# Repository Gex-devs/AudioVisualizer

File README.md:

# STM32 Audio visualizer DOT MATRIX

Audio Visualizer based on STM32 bluepill utilizing Fast FFT and hacky trick to make the Matrix LED working nicely together. 

## Compact Size

Made a Add-on type PCB that laches on the back of the LED matrix.

## Components 
The Audio Visualizer features Real-time audio visualization with Fast Fourier Transform (FFT) to accurately visualize real audio frequencies rather than just detecting high or low noise levels.

* STM32 Bluepill
* MAX4466 Microphone Module
* 8x8 Matrix LED * 4

## Software Used

* [Kicad](https://www.kicad.org/) : PCB Design 
* [STM32MAX](https://www.st.com/en/development-tools/stm32cubemx.html) : Project Configurator 
* [T-filter](http://t-filter.engineerjs.com/) : Desgning Fir filter

## Tools Used

* Lab power supply
* Oscilloscope 
* ST-LINK/V2 debugger

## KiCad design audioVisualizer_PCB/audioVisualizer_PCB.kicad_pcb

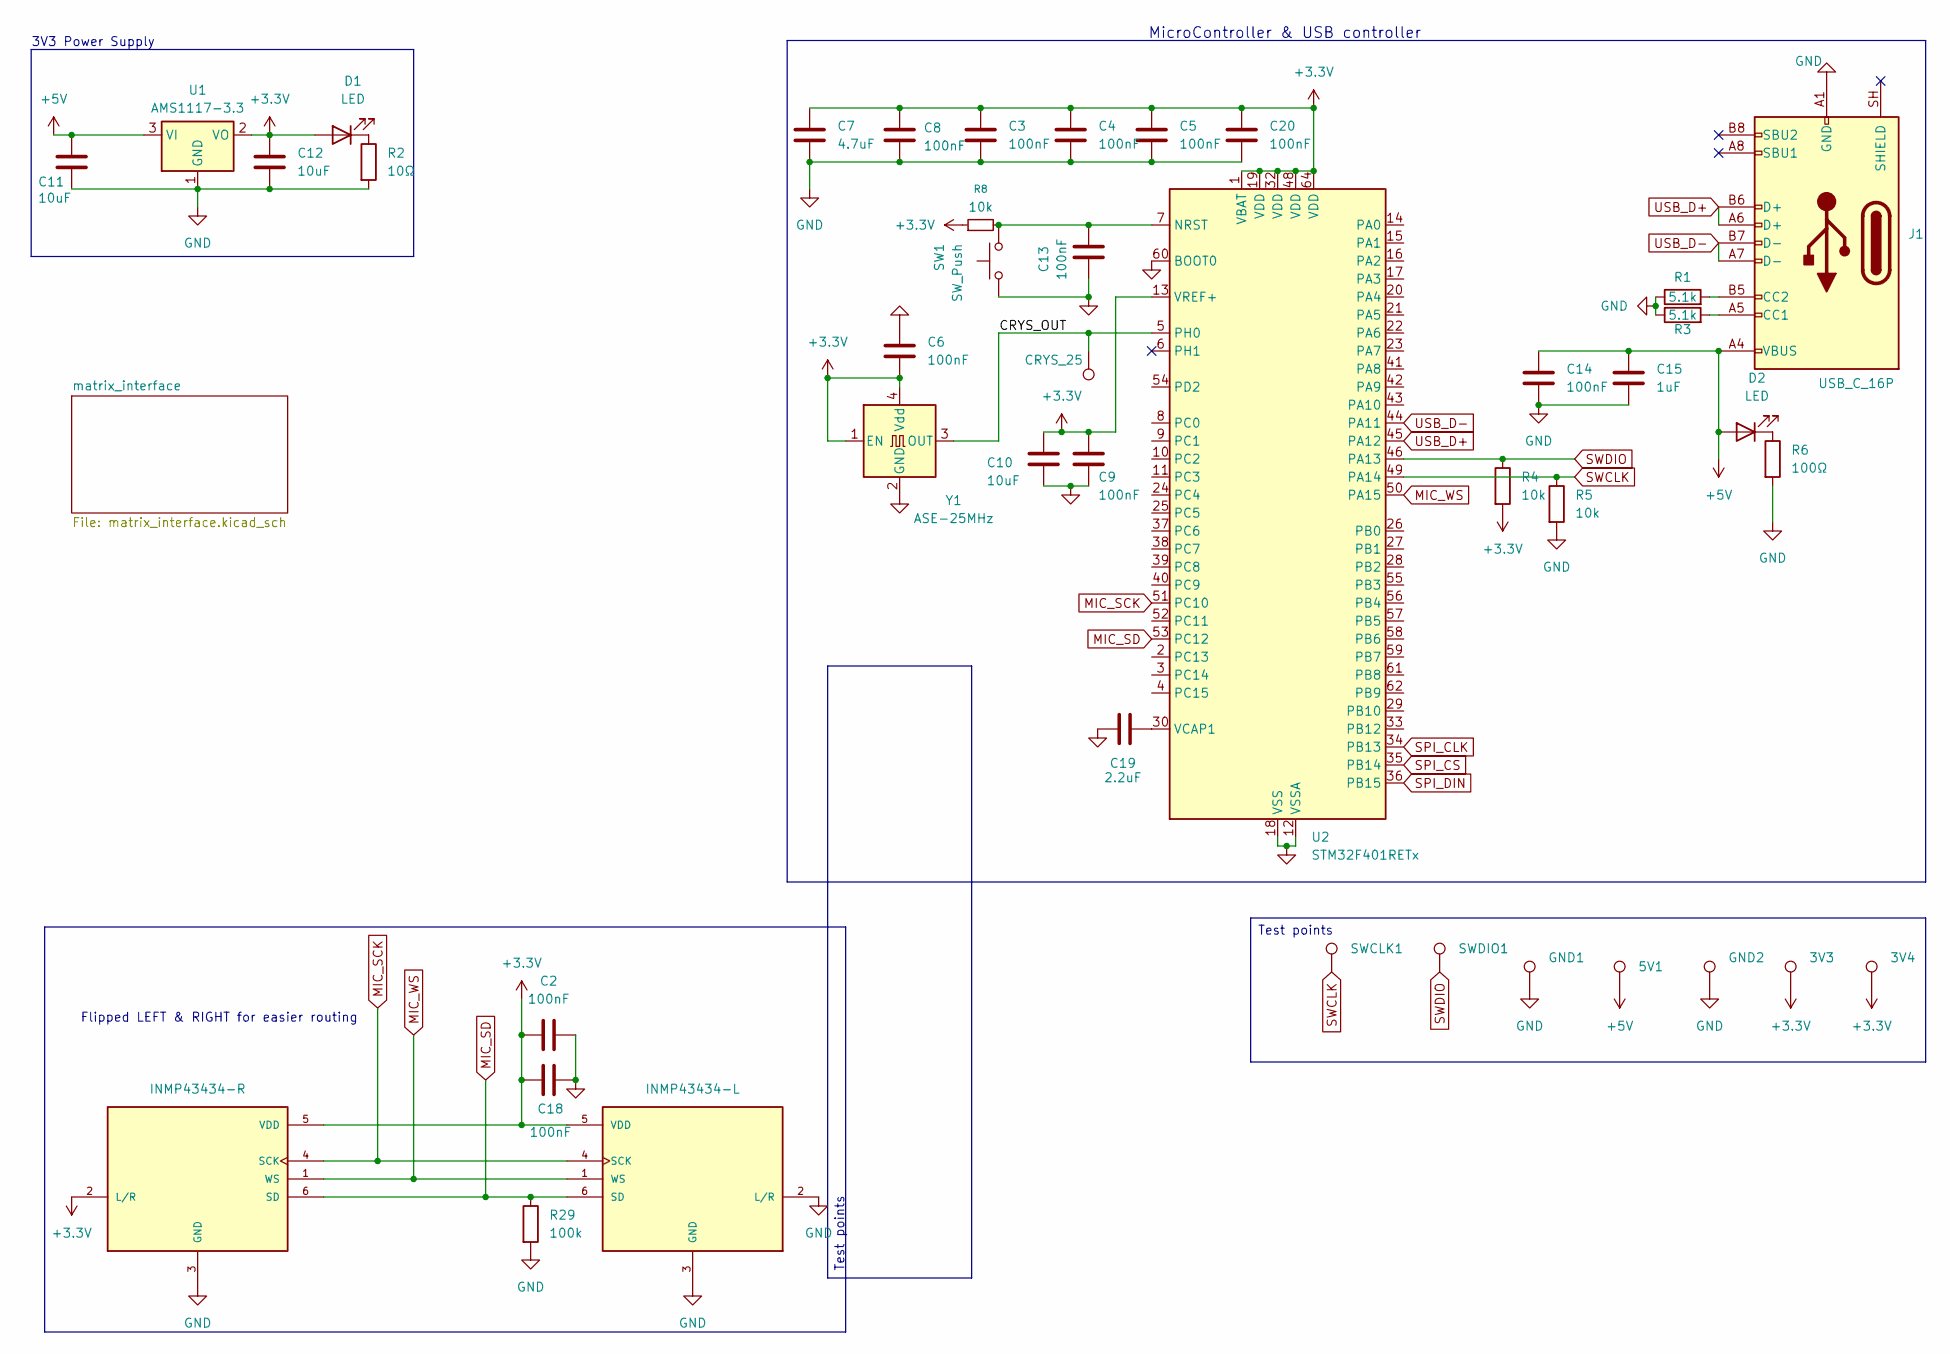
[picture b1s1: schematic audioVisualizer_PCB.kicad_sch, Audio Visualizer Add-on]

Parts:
3V3, 3V4, 5V1: TestPoint_Keystone_5015_Micro_Mini
C2, C3, C6, C8, C9, C13, C18, C20: 100nF; C_0805_2012Metric
C4, C5, C14: 100nF; C_0402_1005Metric
C7: 4.7uF; C_0805_2012Metric
C10, C11, C12: 10uF; C_0805_2012Metric
C15: 1uF; C_0402_1005Metric
C19: 2.2uF; C_0402_1005Metric
CRYS_25: CRYS_25; TestPoint_Keystone_5015_Micro_Mini
D1, D2: LED; LED_0805_2012Metric
GND1, GND2: TestPoint_Keystone_5015_Micro_Mini
J1: USB_C_16P; USB_C_Receptacle_GCT_USB4105-xx-A_16P_TopMnt_Horizontal
MK-L1: INMP43434-R; MIC_ICS-43434; PARTREV 1.1
MK-R1: INMP43434-L; MIC_ICS-43434; PARTREV 1.1
R1, R3: 5.1k; R_1206_3216Metric
R2: 10Ω; R_0402_1005Metric
R4, R5, R8: 10k; R_0805_2012Metric
R6: 100Ω; R_0805_2012Metric
R29: 100k; R_0805_2012Metric
SW1: SW_Push; SW_SPST_TS-1088-xR020
SWCLK1: TestPoint_Keystone_5015_Micro_Mini
SWDIO1: TestPoint_Keystone_5015_Micro_Mini
U1: AMS1117-3.3; SOT-223-3_TabPin2
U2: STM32F401RETx; LQFP-64_10x10mm_P0.5mm
Y1: ASE-25MHz; Oscillator_SMD_EuroQuartz_XO32-4Pin_3.2x2.5mm

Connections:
+3.3V: 3V3.1 (1_1), 3V4.1 (1_1), C2.1, C3.1, C4.1, C5.1, C6.2, C7.1, C8.1, C9.1, C10.1, C12.1, C18.2, C20.1, D1.2 (A), MK-L1.2 (L/R), MK-L1.5 (VDD), MK-R1.5 (VDD), R4.2, R8.1, U1.2 (VO), U2.1 (VBAT), U2.13 (VREF+), U2.19 (VDD), U2.32 (VDD), U2.48 (VDD), U2.64 (VDD), Y1.1 (EN), Y1.4 (Vdd)
+5V: 5V1.1 (1_1), C11.1, C14.2, C15.1, D2.2 (A), J1.A4 (VBUS), J1.A9 (VBUS), J1.B4 (VBUS), J1.B9 (VBUS), U1.3 (VI); also elsewhere on the board
/CRYS_OUT: CRYS_25.1 (1_1), U2.5 (PH0), Y1.3 (OUT)
GND: C2.2, C3.2, C4.2, C5.2, C6.1, C7.2, C8.2, C9.2, C10.2, C11.2, C12.2, C13.2, C14.1, C15.2, C18.1, C19.2, C20.2, GND1.1 (1_1), GND2.1 (1_1), J1.A1 (GND), J1.A12 (GND), J1.B1 (GND), J1.B12 (GND), MK-L1.3 (GND), MK-R1.2 (L/R), MK-R1.3 (GND), R1.1, R2.2, R3.1, R5.2, R6.2, R29.2, SW1.1, U1.1 (GND), U2.12 (VSSA), U2.18 (VSS), U2.31 (VSS), U2.47 (VSS), U2.60 (BOOT0), U2.63 (VSS), Y1.2 (GND); also elsewhere on the board
MIC_SCK: MK-L1.4 (SCK), MK-R1.4 (SCK), U2.51 (PC10)
MIC_SD: MK-L1.6 (SD), MK-R1.6 (SD), R29.1, U2.53 (PC12)
MIC_WS: MK-L1.1 (WS), MK-R1.1 (WS), U2.50 (PA15)
unnamed: D1.1 (K), R2.1
unnamed: D2.1 (K), R6.1
unnamed: J1.A5 (CC1), R3.2
unnamed: J1.B5 (CC2), R1.2
unnamed: C13.1, R8.2, SW1.2, U2.7 (NRST)
unnamed: C19.1, U2.30 (VCAP1)
SPI_CLK: U2.34 (PB13); also elsewhere on the board
SPI_CS: U2.35 (PB14); also elsewhere on the board
SPI_DIN: U2.36 (PB15); also elsewhere on the board
SWCLK: R5.1, SWCLK1.1 (1_1), U2.49 (PA14)
SWDIO: R4.1, SWDIO1.1 (1_1), U2.46 (PA13)
USB_D+: J1.A6 (D+), J1.B6 (D+), U2.45 (PA12)
USB_D-: J1.A7 (D-), J1.B7 (D-), U2.44 (PA11)

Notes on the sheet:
MicroController & USB controller
3V3 Power Supply
Flipped LEFT & RIGHT for easier routing
Test points

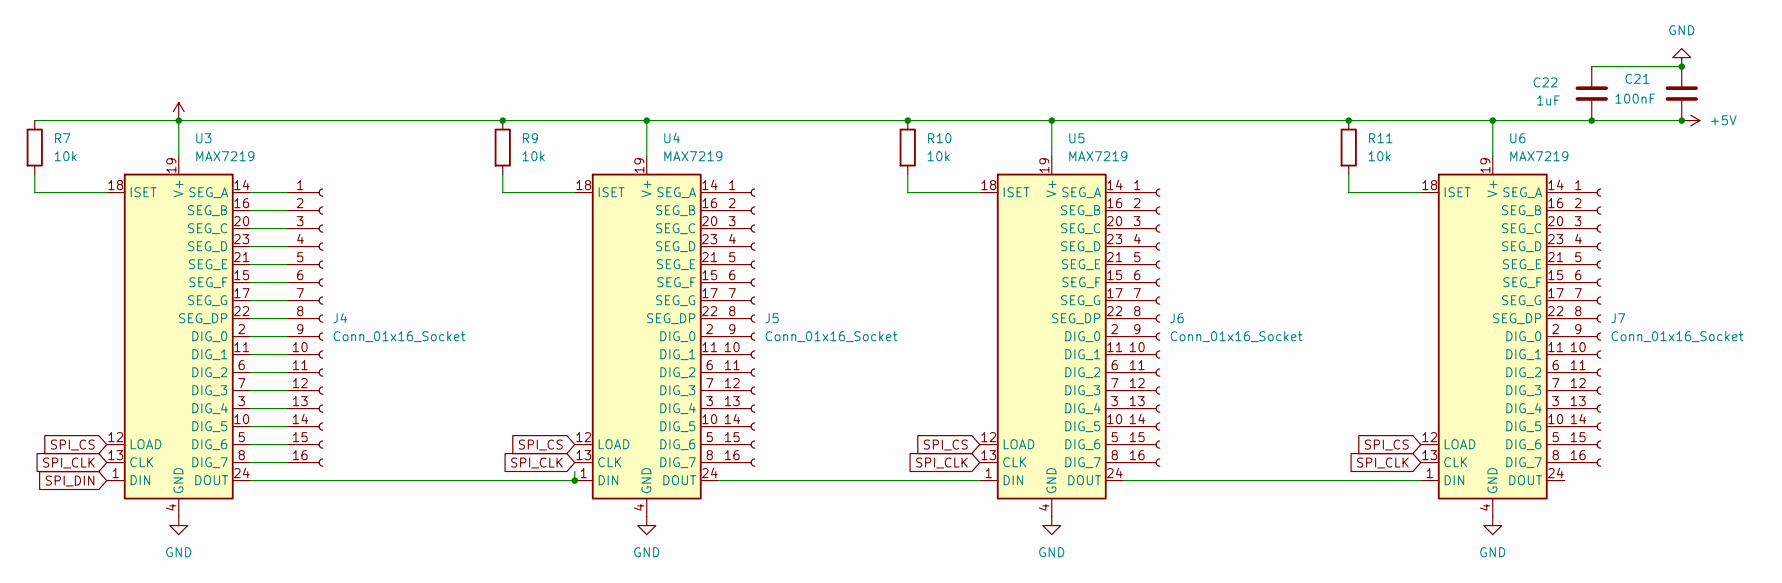
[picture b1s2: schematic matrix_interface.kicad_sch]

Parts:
C21: 100nF; C_0805_2012Metric
C22: 1uF; C_0805_2012Metric
J4, J5, J6, J7: Conn_01x16_Socket; DISPLAY_TA08-81GWA
R7, R9, R10, R11: 10k
U3, U4, U5, U6: MAX7219; SOIC-24W_7.5x15.4mm_P1.27mm

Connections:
+5V: C21.2, C22.1, R7.1, R9.1, R10.1, R11.1, U3.19 (V+), U4.19 (V+), U5.19 (V+), U6.19 (V+); also elsewhere on the board
GND: C21.1, C22.2, U3.4 (GND), U3.9 (GND), U4.4 (GND), U4.9 (GND), U5.4 (GND), U5.9 (GND), U6.4 (GND), U6.9 (GND); also elsewhere on the board
unnamed: J4.1, U3.14 (SEG_A)
unnamed: J4.2, U3.16 (SEG_B)
unnamed: J4.3, U3.20 (SEG_C)
unnamed: J4.4, U3.23 (SEG_D)
unnamed: J4.5, U3.21 (SEG_E)
unnamed: J4.6, U3.15 (SEG_F)
unnamed: J4.7, U3.17 (SEG_G)
unnamed: J4.8, U3.22 (SEG_DP)
unnamed: J4.9, U3.2 (DIG_0)
unnamed: J4.10, U3.11 (DIG_1)
unnamed: J4.11, U3.6 (DIG_2)
unnamed: J4.12, U3.7 (DIG_3)
unnamed: J4.13, U3.3 (DIG_4)
unnamed: J4.14, U3.10 (DIG_5)
unnamed: J4.15, U3.5 (DIG_6)
unnamed: J4.16, U3.8 (DIG_7)
unnamed: J5.1, U4.14 (SEG_A)
unnamed: J5.2, U4.16 (SEG_B)
unnamed: J5.3, U4.20 (SEG_C)
unnamed: J5.4, U4.23 (SEG_D)
unnamed: J5.5, U4.21 (SEG_E)
unnamed: J5.6, U4.15 (SEG_F)
unnamed: J5.7, U4.17 (SEG_G)
unnamed: J5.8, U4.22 (SEG_DP)
unnamed: J5.9, U4.2 (DIG_0)
unnamed: J5.10, U4.11 (DIG_1)
unnamed: J5.11, U4.6 (DIG_2)
unnamed: J5.12, U4.7 (DIG_3)
unnamed: J5.13, U4.3 (DIG_4)
unnamed: J5.14, U4.10 (DIG_5)
unnamed: J5.15, U4.5 (DIG_6)
unnamed: J5.16, U4.8 (DIG_7)
unnamed: J6.1, U5.14 (SEG_A)
unnamed: J6.2, U5.16 (SEG_B)
unnamed: J6.3, U5.20 (SEG_C)
unnamed: J6.4, U5.23 (SEG_D)
unnamed: J6.5, U5.21 (SEG_E)
unnamed: J6.6, U5.15 (SEG_F)
unnamed: J6.7, U5.17 (SEG_G)
unnamed: J6.8, U5.22 (SEG_DP)
unnamed: J6.9, U5.2 (DIG_0)
unnamed: J6.10, U5.11 (DIG_1)
unnamed: J6.11, U5.6 (DIG_2)
unnamed: J6.12, U5.7 (DIG_3)
unnamed: J6.13, U5.3 (DIG_4)
unnamed: J6.14, U5.10 (DIG_5)
unnamed: J6.15, U5.5 (DIG_6)
unnamed: J6.16, U5.8 (DIG_7)
unnamed: J7.1, U6.14 (SEG_A)
unnamed: J7.2, U6.16 (SEG_B)
unnamed: J7.3, U6.20 (SEG_C)
unnamed: J7.4, U6.23 (SEG_D)
unnamed: J7.5, U6.21 (SEG_E)
unnamed: J7.6, U6.15 (SEG_F)
unnamed: J7.7, U6.17 (SEG_G)
unnamed: J7.8, U6.22 (SEG_DP)
unnamed: J7.9, U6.2 (DIG_0)
unnamed: J7.10, U6.11 (DIG_1)
unnamed: J7.11, U6.6 (DIG_2)
unnamed: J7.12, U6.7 (DIG_3)
unnamed: J7.13, U6.3 (DIG_4)
unnamed: J7.14, U6.10 (DIG_5)
unnamed: J7.15, U6.5 (DIG_6)
unnamed: J7.16, U6.8 (DIG_7)
unnamed: U3.24 (DOUT), U4.1 (DIN)
unnamed: R7.2, U3.18 (ISET)
unnamed: U4.24 (DOUT), U5.1 (DIN)
unnamed: R9.2, U4.18 (ISET)
unnamed: U5.24 (DOUT), U6.1 (DIN)
unnamed: R10.2, U5.18 (ISET)
unnamed: R11.2, U6.18 (ISET)
SPI_CLK: U3.13 (CLK), U4.13 (CLK), U5.13 (CLK), U6.13 (CLK); also elsewhere on the board
SPI_CS: U3.12 (LOAD), U4.12 (LOAD), U5.12 (LOAD), U6.12 (LOAD); also elsewhere on the board
SPI_DIN: U3.1 (DIN); also elsewhere on the board

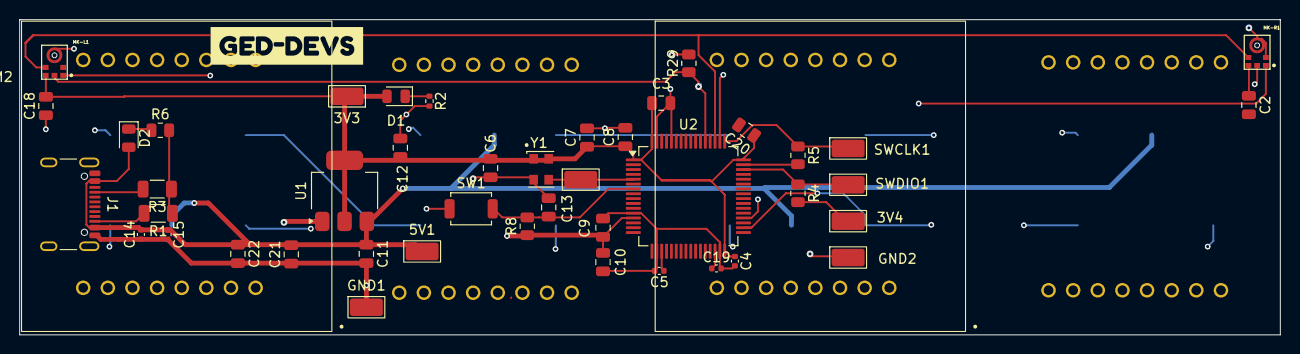
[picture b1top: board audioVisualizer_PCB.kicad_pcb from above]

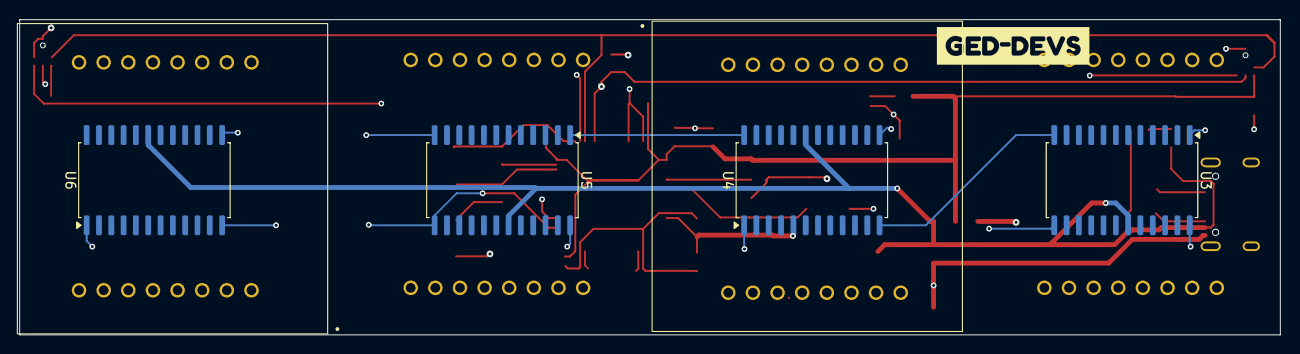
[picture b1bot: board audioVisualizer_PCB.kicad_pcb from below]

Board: 4 copper layers, 130.0 x 32.5 mm, 54 parts (7 on the bottom side), 87 nets.

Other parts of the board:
kibuzzard-69F6314F, kibuzzard-69F6314F#2: G***; kibuzzard-69F6314F

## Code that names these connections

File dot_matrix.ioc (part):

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Mcu.Name=STM32F401R(D-E)Tx
Mcu.Package=LQFP64
Mcu.UserName=STM32F401RETx
PA0-WKUP.Signal=S_TIM2_CH1_ETR
PA11.Mode=Host_Only
PA11.Signal=USB_OTG_FS_DM
PA12.Mode=Host_Only
PA12.Signal=USB_OTG_FS_DP
PA13.Mode=Serial_Wire
PA13.Signal=SYS_JTMS-SWDIO
PA14.Mode=Serial_Wire
PA14.Signal=SYS_JTCK-SWCLK
PA15.Mode=Half_Duplex_Master
PA15.Signal=I2S3_WS
PA9.Mode=Activate_VBUS
PA9.Signal=USB_OTG_FS_VBUS
PB13.Mode=Simplex_Bidirectional_Master
PB13.Signal=SPI2_SCK
PB14.Signal=GPIO_Output
PB15.Mode=Simplex_Bidirectional_Master
PB15.Signal=SPI2_MOSI
PC10.Mode=Half_Duplex_Master
PC10.Signal=I2S3_CK
PC12.Mode=Half_Duplex_Master
PC12.Signal=I2S3_SD
PH0\ -\ OSC_IN.Mode=HSE-External-Clock-Source
PH0\ -\ OSC_IN.Signal=RCC_OSC_IN
PH1\ -\ OSC_OUT.Mode=HSE-External-Clock-Source
PH1\ -\ OSC_OUT.Signal=RCC_OSC_OUT
RCC.HSE_VALUE=25000000
RCC.SYSCLKFreq_VALUE=84000000
RCC.SYSCLKSource=RCC_SYSCLKSOURCE_PLLCLK
board=custom

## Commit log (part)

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2025-04-11 init
2025-04-20 Working module with LED matrix library modification
2025-04-20 Added video and image
2025-07-30 added the working libraries
2025-08-01 applied hann window and added high-pass filter, good visuals
2025-08-01 updated gitignore
2025-08-01 fixed visual mapping, Issue still in Bar index 0 - 10
2025-08-08 added filter, updated ReadME, added PCB
2025-08-08 updated read me
2025-08-08 Moved the interactive BOM to root for deployment
2025-08-19 added fritzing project for prototype
2025-08-19 added image of the Printed pcb
2025-08-28 unfinished workflow and update on the TH of the PCB footprint
2025-08-28 Fixed headerpin diameter, updated workflow
2025-08-28 workflow fix
2025-08-28 Update schematic preview [skip ci]
2025-08-28 testing workflow
2025-10-08 Added additional omni-directional smd mic, not routed or programmed
2026-01-30 update on readme
2026-02-14 break em out
2026-03-20 removed big video file
2026-04-14 updated setting to include all libraries; was causing issues during compilation
2026-04-14 migration to stm32f401
2026-04-20 changed mcu; implemented i2s succesfully; working fft; working visualizer; fixed clock issue; visualizer needs enhancement
2026-04-21 added rebinning but needs polishing
2026-04-22 clean up and similification
2026-04-25 embeddeding the mcu is harder than I thought
2026-04-30 added stereo mics; setup usb-c;fixed timer issue for led matrix; using external clock
2026-05-02 finished pcb ready for production
2026-05-02 updated preview video
2026-05-02 updated interactive bom
2026-05-03 removed history
2026-05-06 updated kicad release to the latest version
2026-05-06 dummy test for github action
2026-05-15 reflect on code as well
2026-05-18 removed unused schematic
2026-06-09 manually routed the tracks; switch LEFT/RIGHT mic
2026-06-24 added cap for vref pin
